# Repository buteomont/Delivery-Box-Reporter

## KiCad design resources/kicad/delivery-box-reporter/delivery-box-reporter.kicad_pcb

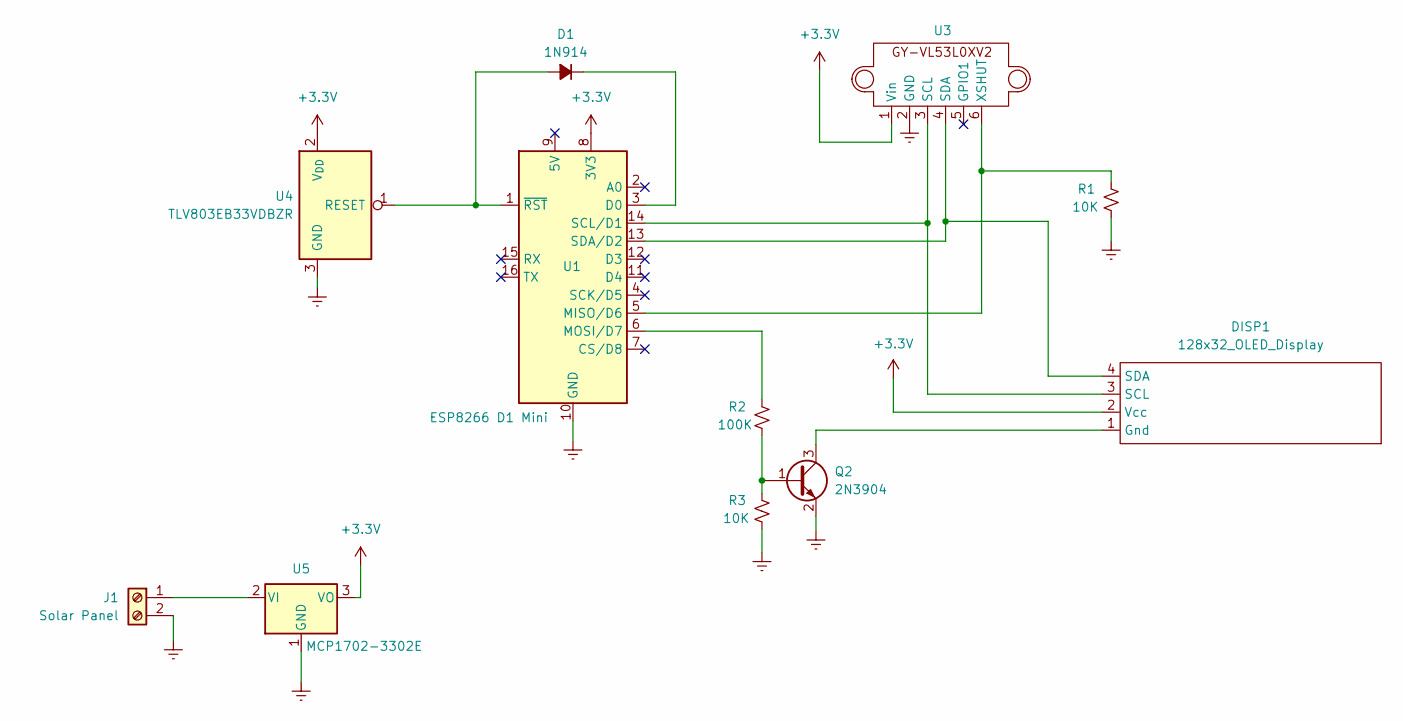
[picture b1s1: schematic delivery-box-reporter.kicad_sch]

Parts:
D1: 1N914; R_0805_2012Metric
DISP1: 128x32_OLED_Display; OLED_0.91_128x32
J1: Solar Panel; KF350 2 Pin Terminal Block
Q2: 2N3904; MMBT3904-7-F_SOT-23-3
R1, R3: 10K; R_0805_2012Metric
R2: 100K; R_0805_2012Metric
U1: ESP8266 D1 Mini; WEMOS_D1_mini_light
U3: GY-VL53LOX-V2
U4: TLV803EB33VDBZR; SOT-23
U5: MCP1702-3302E; TO-92_Inline

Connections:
+3.3V: DISP1.2 (Vcc), U1.8 (3V3), U3.1 (Vin), U4.2 (V_{DD}), U5.3 (VO); also elsewhere on the board
Earth: J1.2, Q2.2 (E), R1.1, R3.1, U1.10 (GND), U3.2 (GND), U4.3 (GND), U5.1 (GND); also elsewhere on the board
unnamed: D1.2 (A), U1.1 (~RST), U4.1 (RESET)
unnamed: D1.1 (K), U1.3 (D0)
unnamed: DISP1.1 (Gnd), Q2.3 (C)
unnamed 5: DISP1.3 (SCL), U1.14 (SCL/D1), U3.3 (SCL); also elsewhere on the board
unnamed 6: DISP1.4 (SDA), U1.13 (SDA/D2), U3.4 (SDA); also elsewhere on the board
unnamed: J1.1, U5.2 (VI)
unnamed: Q2.1 (B), R2.1, R3.2
unnamed 9: R1.2, U1.5 (MISO/D6), U3.6 (XSHUT); also elsewhere on the board
unnamed: R2.2, U1.6 (MOSI/D7)

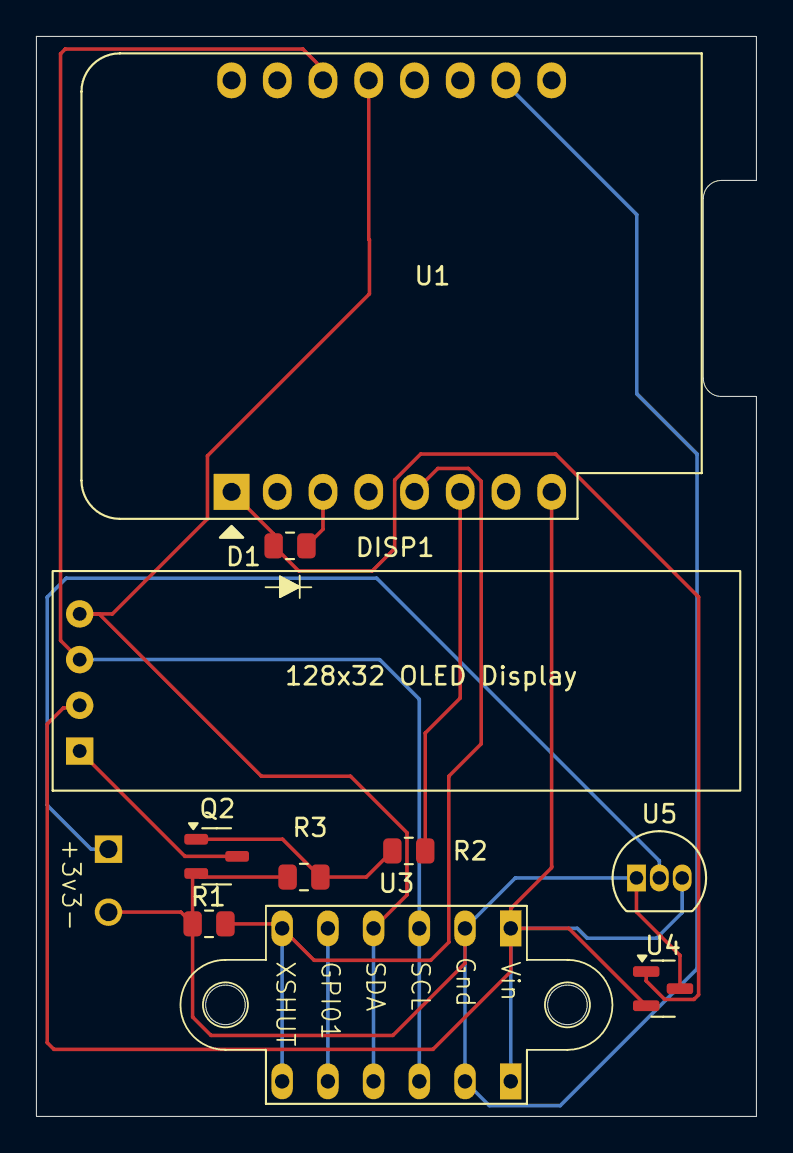
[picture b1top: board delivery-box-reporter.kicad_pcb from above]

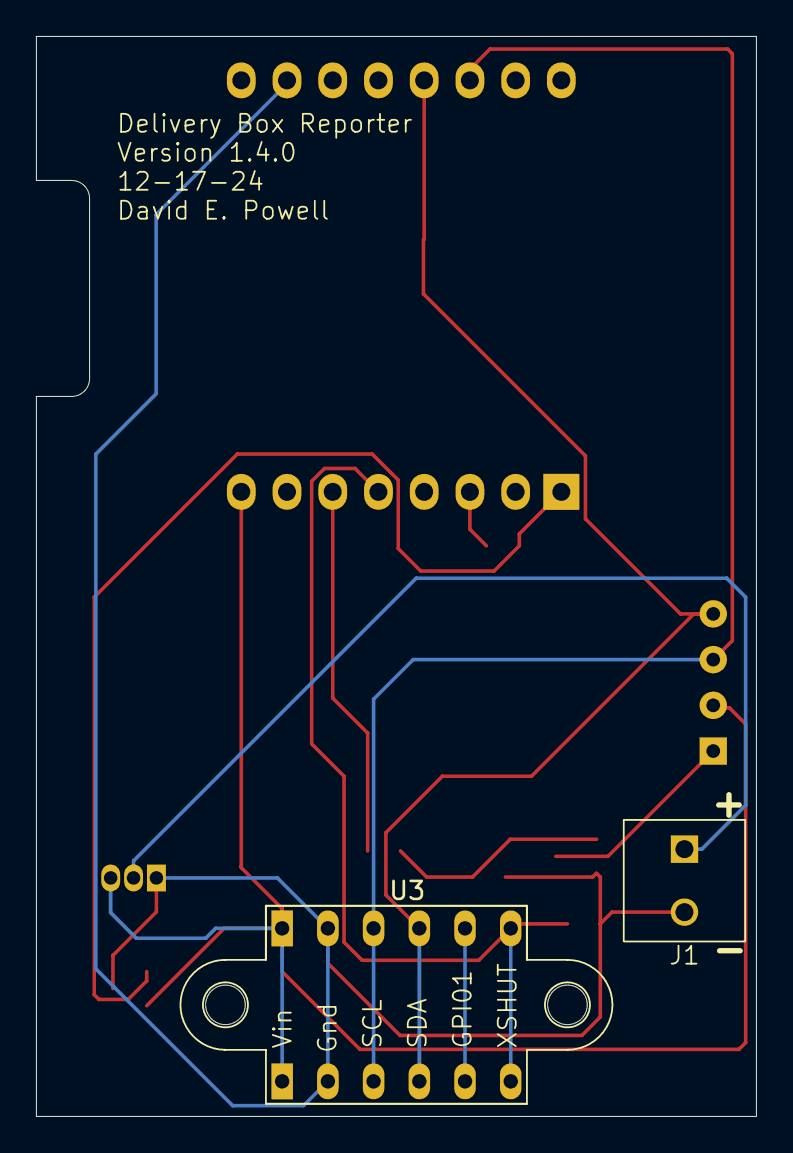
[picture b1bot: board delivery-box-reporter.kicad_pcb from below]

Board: 2 copper layers, 40.0 x 60.0 mm, 12 parts (2 on the bottom side), 11 nets.

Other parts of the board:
U3#2: GY-VL53LOX-V2

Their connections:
+3.3V: U3#2.1 (Vin); also elsewhere on the board
Earth: U3#2.2 (GND); also elsewhere on the board
unnamed 5: U3#2.3 (SCL); also elsewhere on the board
unnamed 6: U3#2.4 (SDA); also elsewhere on the board
unnamed 9: U3#2.6 (XSHUT); also elsewhere on the board

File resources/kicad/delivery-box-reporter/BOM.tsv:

Reference	Value	Datasheet	Footprint	Qty	DNP
D1	1N914	~	Resistor_SMD:R_0805_2012Metric	1	
DISP1	128x32_OLED_Display		Display:OLED_0.91_128x32	1	
J1	Solar Panel	~	Davids_Footprints:KF350 2 Pin Terminal Block	1	
Q2	2N3904	https://www.onsemi.com/pub/Collateral/2N3903-D.PDF	Package_TO_SOT_SMD:SOT-23	1	
R1,R3	10K	~	Resistor_SMD:R_0805_2012Metric	2	
R2	100K	~	Resistor_SMD:R_0805_2012Metric	1	
U1	ESP8266 D1 Mini	https://wiki.wemos.cc/products:d1:d1_mini#documentation	Module:WEMOS_D1_mini_light	1	
U3	~		Sensor_Distance:GY-VL53LOX-V2	1	
U4	TLV803EB33VDBZR	https://www.ti.com/lit/ds/symlink/tlv803e.pdf	Package_TO_SOT_SMD:SOT-23	1	
U5	MCP1702-3302E	http://ww1.microchip.com/downloads/en/DeviceDoc/20001826D.pdf	Package_TO_SOT_THT:TO-92_Inline	1

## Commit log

2024-12-02 added some ignore files and small code changes
2024-12-02 Remove ignored files from version control
2024-12-02 removed ignored files
2024-12-16 Updated PCB
2024-12-18 Changes to board and minor code changes.
2024-12-18 Combined overloaded show() functions
2024-12-18 Added funtion to invert the display
2024-12-19 Added RSSI indicator, wifi address report
2024-12-19 modified wifi connection code for better efficiency
2024-12-21 Clear rtc timer every hour
2024-12-21 Reduced display text size when wifi icon is showing
2024-12-21 A bug in loop() prevented distance check
